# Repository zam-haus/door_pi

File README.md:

# door_pi

Controls electric door locks/openers via GPIO or a USB-serial microcontroller,
and exposes them over MQTT (see `door_manager/`). `uc/` is the firmware that
runs on the microcontroller for the USB HAL variant.

## Running the simulation

`run_simulation.py` runs the real `door_manager` (including a real MQTT
connection) against an in-process simulated microcontroller
(`DoorHalUsbSimulatedUc` in `door_manager/door_hal.py`), so you can exercise
the whole stack without any hardware attached.

1. Install both `door_manager` and `uc` as editable packages into the project
   venv (only needed once, or after changing dependencies):

   ```sh
   uv sync
   ```

2. Start a local MQTT broker with the compose file in `testing/`:

   ```sh
   (cd testing; podman compose up -d --build)   # or: docker compose up -d --build
   ```

   This builds `testing/mosquitto/Dockerfile` (based on `eclipse-mosquitto`,
   with the config and password file baked in — see below) and starts it on
   `127.0.0.1:8001`, with auth for user/pass `test`/`test` — matching
   `door_manager/config.json.example-usb`, which the simulation uses by
   default.

   > If you have the `mosquitto` package installed on the host, its AppArmor
   > profile attaches by executable path (`/usr/sbin/mosquitto`), which
   > confines *this* container's mosquitto too on exec and blocks it from
   > reading its own config — regardless of container boundaries or
   > `--security-opt apparmor=unconfined`. `testing/mosquitto/Dockerfile`
   > works around this by copying the binary to a different path before
   > running it, so the host profile's attachment never matches. That's also
   > why the config/password file are baked into the image via `COPY`
   > rather than bind-mounted: the same host profile only allows the
   > mosquitto binary to read `/etc/mosquitto/**`.

3. Run the simulation:

   ```sh
   uv run run_simulation.py
   ```

   Pass `-c FILE` to point it at a different `door_manager` config.

   By default this also drives random simulated events, so you don't have
   to trigger everything by hand: the mode-switch buttons (`in1`/`in2`,
   `cycle-forward-input`/`cycle-backward-input` in the config) get pressed
   at random, and a simulated door-position sensor reacts to open impulses
   on `out3` -- except sometimes (by default 20% of the time) it doesn't,
   to exercise a flaky-sensor path. Every simulated event is logged with a
   `SIM:` prefix. Tune or disable this with:

   ```
   --no-random-events               turn it off entirely
   --button-min=SECONDS              min delay between button presses [default: 1.5]
   --button-max=SECONDS              max delay between button presses [default: 4.0]
   --pulse-hold=SECONDS               how long a button press is held [default: 0.3]
   --malfunction-rate=RATE            chance (0-1) the door sensor misses an open [default: 0.2]
   --sensor-check-interval=SECONDS   how often the sensor polls for an open impulse [default: 0.05]
   ```

4. When done, stop the broker:

   ```sh
   cd testing
   podman compose down   # or: docker compose down
   ```

## Sending MQTT messages

The `eclipse-mosquitto` image bundles the `mosquitto_pub`/`mosquitto_sub`
CLI tools, so you don't need to install an MQTT client locally — just run
them inside the broker container via `podman compose exec` (from the
`testing/` directory, with the broker already up). Use `localhost`/`1883`
(the container's own view of the broker), not the host-mapped `8001`.

Watch everything the door publishes and any commands sent to it:

```sh
(cd testing; podman compose exec mosquitto mosquitto_sub -h localhost -p 1883 \
  -u test -P test -t 'door/#' -v)
```

Send an open command (door-id `1234`, matching
`door_manager/config.json.example-usb`) — `not_after` is a Unix timestamp
the request must arrive before:

```sh
(cd testing; podman compose exec mosquitto mosquitto_pub -h localhost -p 1883 \
  -u test -P test -t door/1234/open -m "{\"not_after\": $(($(date +%s) + 60))}")
```

With the simulation running, this should trigger `DoorManager.open_door()`
and impulse the configured output GPIOs on the simulated microcontroller.

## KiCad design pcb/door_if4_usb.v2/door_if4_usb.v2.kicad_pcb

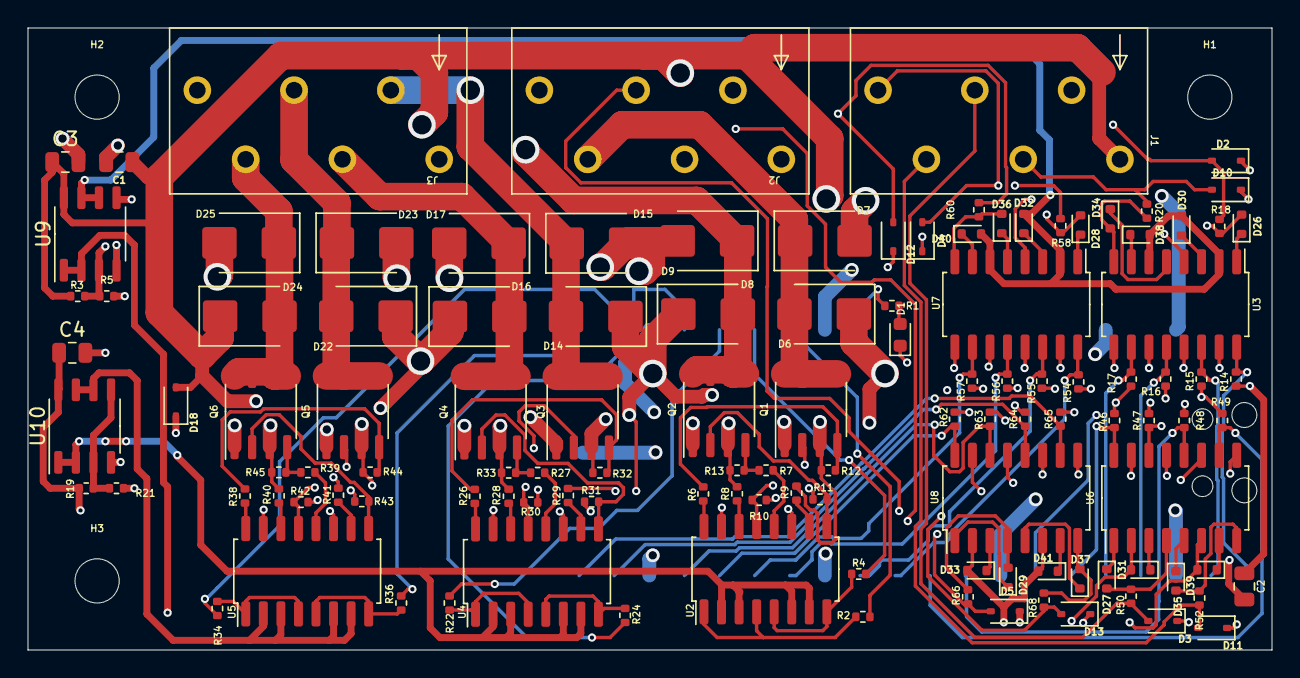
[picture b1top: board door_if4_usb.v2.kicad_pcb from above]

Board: 4 copper layers, 90.0 x 45.0 mm, 123 parts (1 on the bottom side), 102 nets.

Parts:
C1, C2, C3, C4: 100n/50V; C_0805_2012Metric
D1: LED; LED_0603_1608Metric
D2, D3, D4, D5, D10, D11, D12, D13, D18: LY323DC24; D_SOD-323
D6, D7, D8, D9, D14, D15, D16, D17, D22, D23, D24, D25: SS24B; D_SMB
D26, D27, D28, D29, D30, D31, D32, D33, D34, D35, D36, D37, D38, D39, D40, D41: D; D_SOD-523
H1, H2, H3: MountingHole; MountingHole_3.2mm_M3_DIN965
J1, J2, J3: WAGO 250-206; WAGO-250-206
Q1, Q2, Q3, Q4, Q5, Q6: IRF7343; SO-8_3.9x4.9mm_P1.27mm
R1: 470; R_0402_1005Metric
R2, R4, R22, R24, R34, R36: 120; R_0402_1005Metric
R3, R5, R6, R7, R8, R9, R10, R11, R12, R13, R19, R21, R26, R27, R28, R29, R30, R31, R32, R33, R38, R39, R40, R41, R42, R43, R44, R45: 10k; R_0402_1005Metric
R14, R15, R16, R17, R18, R20, R46, R47, R48, R49, R50, R52, R54, R55, R56, R57, R58, R60, R62, R63, R64, R65, R66, R68: 2k2; R_0402_1005Metric
U1: Pico; RPi_Pico_SMDonly
U2, U3, U4, U5, U6, U7, U8: LTV-247; SOP-16_4.4x10.4mm_P1.27mm
U9, U10: COS2171; SOP-8_3.9x4.9mm_P1.27mm

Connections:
+3V3: C2.1, C4.1, R14.1, R15.1, R16.1, R17.1, R19.1, R46.1, R47.1, R48.1, R49.1, R54.1, R55.1, R56.1, R57.1, R62.1, R63.1, R64.1, R65.1, U1.36 (3V3), U10.8 (V+)
+24V: C1.1, C3.1, D6.1 (K), D8.1 (K), D14.1 (K), D16.1 (K), D18.2 (A2), D22.1 (K), D24.1 (K), J1.1, J2.1, Q1.3 (S2), Q2.3 (S2), Q3.3 (S2), Q4.3 (S2), Q5.3 (S2), Q6.3 (S2), R3.1, R8.2, R9.2, R12.2, R13.2, R28.2, R29.2, R32.2, R33.2, R40.2, R41.2, R44.2, R45.2, U9.8 (V+)
GND: C2.2, C4.2, D1.1 (K), R21.2, U1.3 (GND), U1.8 (GND), U1.13 (GND), U1.18 (GND), U1.23 (GND), U1.28 (GND), U1.38 (GND), U1.42 (GND), U3.9, U3.11, U3.13, U3.15, U6.9, U6.11, U6.13, U6.15, U7.9, U7.11, U7.13, U7.15, U8.9, U8.11, U8.13, U8.15, U10.4 (V-)
GNDA: C1.2, C3.2, D2.1 (A1), D3.1 (A1), D4.1 (A1), D5.1 (A1), D7.2 (A), D9.2 (A), D10.1 (A1), D11.1 (A1), D12.1 (A1), D13.1 (A1), D15.2 (A), D17.2 (A), D18.1 (A1), D23.2 (A), D25.2 (A), J2.6, J3.6, Q1.1 (S1), Q2.1 (S1), Q3.1 (S1), Q4.1 (S1), Q5.1 (S1), Q6.1 (S1), R5.2, R10.1, R11.1, R30.1, R31.1, R42.1, R43.1, U2.11, U2.15, U4.11, U4.15, U5.11, U5.15, U9.4 (V-)
IN1: D2.2 (A2), J1.2, R18.2
IN2: D10.2 (A2), J1.3, R20.2
IN3: D3.2 (A2), J1.4, R50.2
IN4: D11.2 (A2), J1.5, R52.2
IN5: D4.2 (A2), J1.6, R58.2
IN6: D12.2 (A2), J2.2, R60.2
IN7: D5.2 (A2), J2.3, R66.2
IN8: D13.2 (A2), J2.4, R68.2
unnamed: D1.2 (A), R1.1
unnamed: D26.2 (A), R18.1, U3.4
unnamed: D26.1 (K), U3.1
unnamed: D27.2 (A), R50.1, U6.4
unnamed: D27.1 (K), U6.1
unnamed: D28.2 (A), R58.1, U7.4
unnamed: D28.1 (K), U7.1
unnamed: D29.2 (A), R66.1, U8.4
unnamed: D29.1 (K), U8.1
unnamed: D30.1 (K), U3.3
unnamed: D31.1 (K), U6.3
unnamed: D32.1 (K), U7.3
unnamed: D33.1 (K), U8.3
unnamed: D34.2 (A), R20.1, U3.8
unnamed: D34.1 (K), U3.5
unnamed: D35.2 (A), R52.1, U6.8
unnamed: D35.1 (K), U6.5
unnamed: D36.2 (A), R60.1, U7.8
unnamed: D36.1 (K), U7.5
unnamed: D37.2 (A), R68.1, U8.8
unnamed: D37.1 (K), U8.5
unnamed: D38.1 (K), U3.7
unnamed: D39.1 (K), U6.7
unnamed: D40.1 (K), U7.7
unnamed: D41.1 (K), U8.7
unnamed: Q1.2 (G1), R10.2, U2.13
unnamed: Q1.4 (G2), R6.2, R12.1
unnamed: Q2.2 (G1), R11.2, U2.9
unnamed: Q2.4 (G2), R7.2, R13.1
unnamed: Q3.2 (G1), R30.2, U4.13
unnamed: Q3.4 (G2), R26.2, R32.1
unnamed: Q4.2 (G1), R31.2, U4.9
unnamed: Q4.4 (G2), R27.2, R33.1
unnamed: Q5.2 (G1), R42.2, U5.13
unnamed: Q5.4 (G2), R38.2, R44.1
unnamed: Q6.2 (G1), R43.2, U5.9
unnamed: Q6.4 (G2), R39.2, R45.1
unnamed: R2.2, U2.1, U2.4
unnamed: R4.2, U2.5, U2.8
unnamed: R6.1, U2.16
unnamed: R7.1, U2.12
unnamed: R8.1, U2.14
unnamed: R9.1, U2.10
unnamed: R22.2, U4.1, U4.4
unnamed: R24.2, U4.5, U4.8
unnamed: R26.1, U4.16
unnamed: R27.1, U4.12
unnamed: R28.1, U4.14
unnamed: R29.1, U4.10
unnamed: R34.2, U5.1, U5.4
unnamed: R36.2, U5.5, U5.8
unnamed: R38.1, U5.16
unnamed: R39.1, U5.12
unnamed: R40.1, U5.14
unnamed: R41.1, U5.10
unnamed: R3.2, R5.1, U9.3 (+), U9.5 (+)
unnamed: R19.2, R21.1, U10.3 (+), U10.5 (+)
OUT1: D6.2 (A), D7.1 (K), J2.5, Q1.5 (D), Q1.6 (D), Q1.7 (D), Q1.8 (D)
OUT2: D8.2 (A), D9.1 (K), J3.1, Q2.5 (D), Q2.6 (D), Q2.7 (D), Q2.8 (D)
OUT3: D14.2 (A), D15.1 (K), J3.2, Q3.5 (D), Q3.6 (D), Q3.7 (D), Q3.8 (D)
OUT4: D16.2 (A), D17.1 (K), J3.3, Q4.5 (D), Q4.6 (D), Q4.7 (D), Q4.8 (D)
OUT5: D22.2 (A), D23.1 (K), J3.4, Q5.5 (D), Q5.6 (D), Q5.7 (D), Q5.8 (D)
OUT6: D24.2 (A), D25.1 (K), J3.5, Q6.5 (D), Q6.6 (D), Q6.7 (D), Q6.8 (D)
O_LED: R1.2, U1.29 (GPIO22)
S_IN1A: R14.2, U1.1 (GPIO0), U3.16
S_IN1B: R15.2, U1.2 (GPIO1), U3.14
S_IN2A: R16.2, U1.4 (GPIO2), U3.12
S_IN2B: R17.2, U1.5 (GPIO3), U3.10
S_IN3A: R46.2, U1.6 (GPIO4), U6.16
S_IN3B: R47.2, U1.7 (GPIO5), U6.14
S_IN4A: R48.2, U1.9 (GPIO6), U6.12
S_IN4B: R49.2, U1.10 (GPIO7), U6.10
S_IN5A: R54.2, U1.11 (GPIO8), U7.16
S_IN5B: R55.2, U1.12 (GPIO9), U7.14
S_IN6A: R56.2, U1.14 (GPIO10), U7.12
S_IN6B: R57.2, U1.15 (GPIO11), U7.10
S_IN7A: R62.2, U1.16 (GPIO12), U8.16
S_IN7B: R63.2, U1.17 (GPIO13), U8.14
S_IN8A: R64.2, U1.19 (GPIO14), U8.12
S_IN8B: R65.2, U1.20 (GPIO15), U8.10
S_OUT1: R2.1, U1.27 (GPIO21)
S_OUT2: R4.1, U1.26 (GPIO20)
S_OUT3: R22.1, U1.25 (GPIO19)
S_OUT4: R24.1, U1.24 (GPIO18)
S_OUT5: R34.1, U1.22 (GPIO17)
S_OUT6: R36.1, U1.21 (GPIO16)
VmidA: D31.2 (A), D33.2 (A), D39.2 (A), D41.2 (A), U6.2, U6.6, U8.2, U8.6, U9.1, U9.2 (-)
VmidB: D30.2 (A), D32.2 (A), D38.2 (A), D40.2 (A), U3.2, U3.6, U7.2, U7.6, U9.6 (-), U9.7
Vmid_3v3_A: U2.2, U2.3, U2.6, U2.7, U4.2, U4.3, U4.6, U4.7, U10.1, U10.2 (-)
Vmid_3v3_B: U5.2, U5.3, U5.6, U5.7, U10.6 (-), U10.7

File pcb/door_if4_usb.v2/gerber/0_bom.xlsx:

Comment | Designator | Footprint
LY323DC24 | D2,D10,D12,D18,D3,D5,D13,D4,D11 | D_SOD-323
D | D28,D31,D34,D27,D35,D33,D30,D39,D37,D29,D38,D32,D41,D40,D26,D36 | D_SOD-523
SS24B | D24,D7,D22,D9,D16,D25,D8,D23,D17,D14,D15,D6 | D_SMB
10k | R8,R38,R21,R39,R5,R10,R29,R9,R45,R7,R31,R12,R11,R13,R30,R26,R27,R42,R3,R19,R33,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 | R_0402_1005Metric
2k2 | R60,R54,R17,R55,R20,R49,R66,R52,R64,R56,R47,R18,R16,R46,R57,R63,R68,R15,R50,R48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 | R_0402_1005Metric
120 | R22,R4,R2,R24,R36,R34 | R_0402_1005Metric
LTV-247 | U3,U7,U8,U4,U2,U6,U5 | SOP-16_4.4x10.4mm_P1.27mm
IRF7343 | Q4,Q6,Q1,Q5,Q2,Q3 | SO-8_3.9x4.9mm_P1.27mm
100n/50V | C3,C2,C4,C1 | C_0805_2012Metric
LED | D1 | LED_0603_1608Metric
COS2171 | U10,U9 | SOP-8_3.9x4.9mm_P1.27mm
470 | R1 | R_0402_1005Metric

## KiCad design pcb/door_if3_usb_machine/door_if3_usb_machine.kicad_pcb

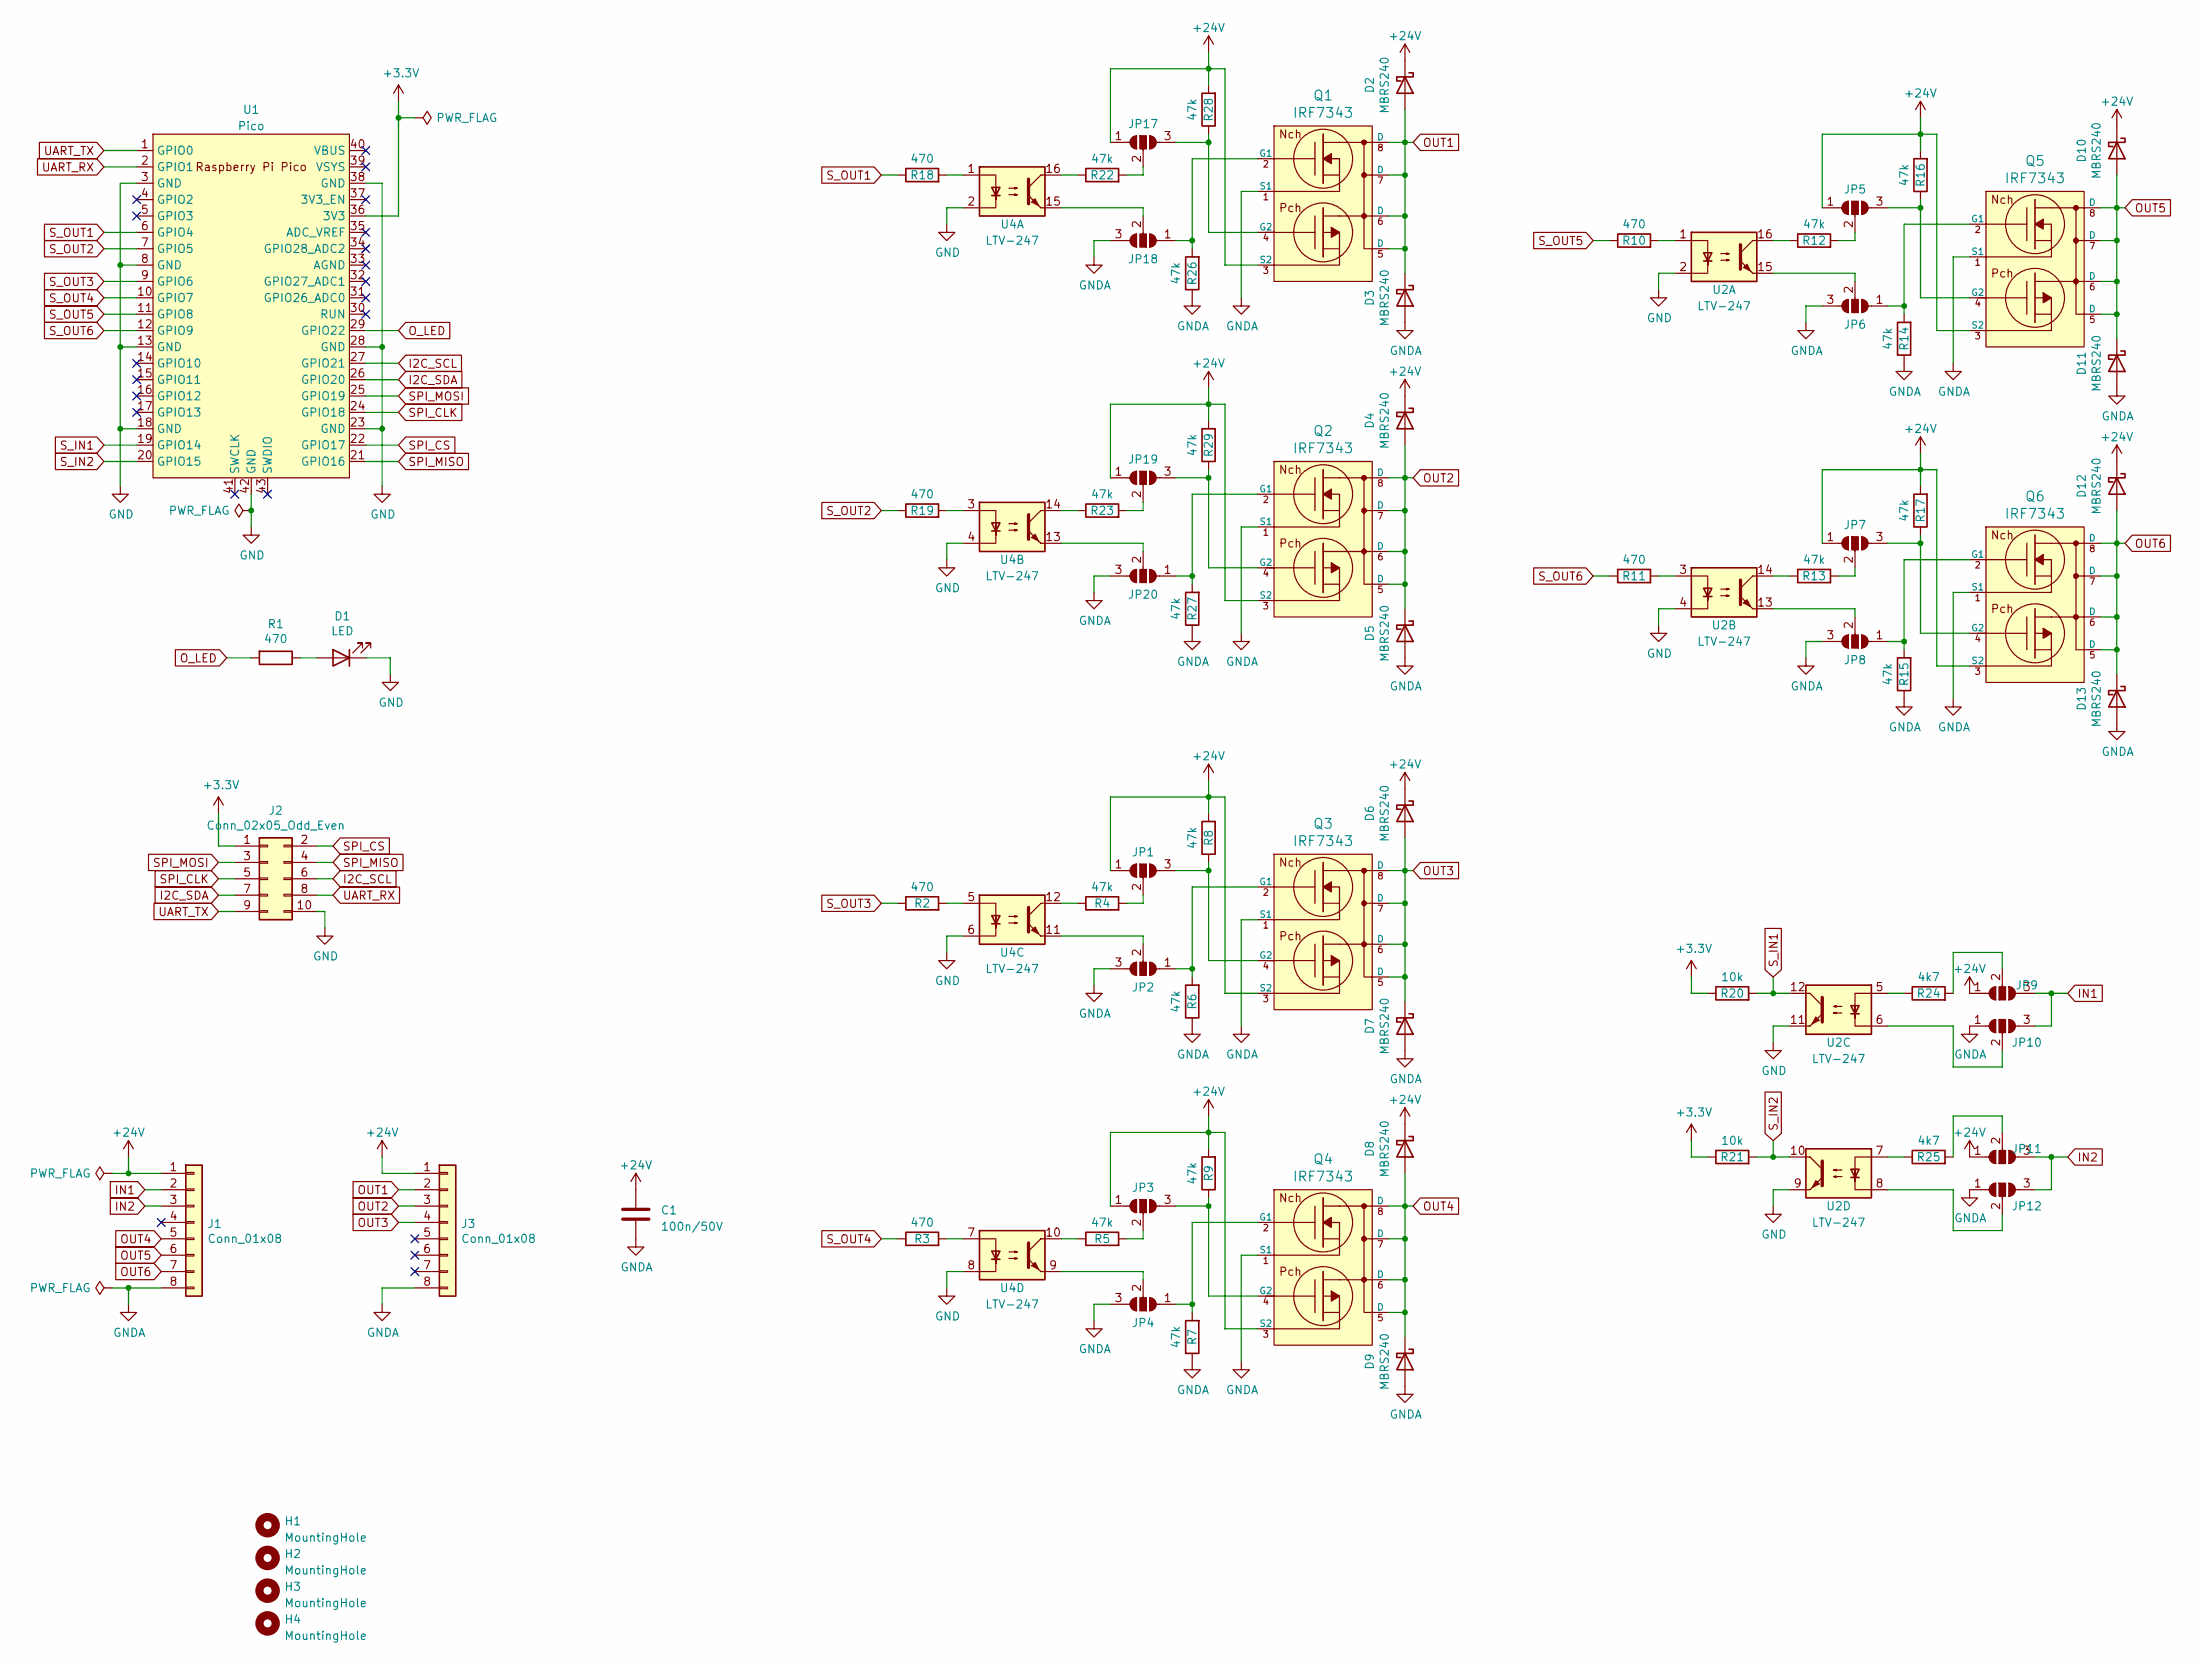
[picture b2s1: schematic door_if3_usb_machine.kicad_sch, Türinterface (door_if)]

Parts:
C1: 100n/50V; C_0603_1608Metric_Pad1.08x0.95mm_HandSolder
D1: LED; LED_0603_1608Metric_Pad1.05x0.95mm_HandSolder
D2, D3, D4, D5, D6, D7, D8, D9, D10, D11, D12, D13: MBRS240; D_SMB_Handsoldering
H1, H2, H3, H4: MountingHole; MountingHole_3.2mm_M3_DIN965
J1, J3: Conn_01x08; LSA-IDC381-8
J2: Conn_02x05_Odd_Even; con-harting-ml-ML10
JP1, JP2, JP3, JP4, JP5, JP6, JP7, JP8, JP9, JP10, JP11, JP12, JP17, JP18, JP19, JP20: SolderJumper_3_Open; SolderJumper-3_P1.3mm_Open_Pad1.0x1.5mm
Q1, Q2, Q3, Q4, Q5, Q6: IRF7343; SO-8_3.9x4.9mm_P1.27mm
R1, R2, R3, R10, R11, R18, R19: 470; R_0603_1608Metric_Pad0.98x0.95mm_HandSolder
R4, R5, R6, R7, R8, R9, R12, R13, R14, R15, R16, R17, R22, R23, R26, R27, R28, R29: 47k; R_0603_1608Metric_Pad0.98x0.95mm_HandSolder
R20, R21: 10k; R_0603_1608Metric_Pad0.98x0.95mm_HandSolder
R24, R25: 4k7; R_0603_1608Metric_Pad0.98x0.95mm_HandSolder
U1: Pico; RPi_Pico_SMDonly
U2, U4: LTV-247; SOP-16_4.4x10.4mm_P1.27mm

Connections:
+3V3: J2.1, R20.1, R21.1, U1.36 (3V3)
+24V: C1.1, D2.1 (K), D4.1 (K), D6.1 (K), D8.1 (K), D10.1 (K), D12.1 (K), J1.1, J3.1, JP1.1 (A), JP3.1 (A), JP5.1 (A), JP7.1 (A), JP9.1 (A), JP11.1 (A), JP17.1 (A), JP19.1 (A), Q1.3 (S2), Q2.3 (S2), Q3.3 (S2), Q4.3 (S2), Q5.3 (S2), Q6.3 (S2), R8.2, R9.2, R16.2, R17.2, R28.2, R29.2
GND: D1.1 (K), J2.10, U1.3 (GND), U1.8 (GND), U1.13 (GND), U1.18 (GND), U1.23 (GND), U1.28 (GND), U1.38 (GND), U1.42 (GND), U2.2, U2.4, U2.9, U2.11, U4.2, U4.4, U4.6, U4.8
GNDA: C1.2, D3.2 (A), D5.2 (A), D7.2 (A), D9.2 (A), D11.2 (A), D13.2 (A), J1.8, J3.8, JP2.3 (B), JP4.3 (B), JP6.3 (B), JP8.3 (B), JP10.1 (A), JP12.1 (A), JP18.3 (B), JP20.3 (B), Q1.1 (S1), Q2.1 (S1), Q3.1 (S1), Q4.1 (S1), Q5.1 (S1), Q6.1 (S1), R6.1, R7.1, R14.1, R15.1, R26.1, R27.1
I2C_SCL: J2.6, U1.27 (GPIO21)
I2C_SDA: J2.7, U1.26 (GPIO20)
IN1: J1.2, JP9.3 (B), JP10.3 (B)
IN2: J1.3, JP11.3 (B), JP12.3 (B)
unnamed: D1.2 (A), R1.1
unnamed: JP1.3 (B), Q3.4 (G2), R8.1
unnamed: JP1.2 (C), R4.2
unnamed: JP2.1 (A), Q3.2 (G1), R6.2
unnamed: JP2.2 (C), U4.11
unnamed: JP3.3 (B), Q4.4 (G2), R9.1
unnamed: JP3.2 (C), R5.2
unnamed: JP4.1 (A), Q4.2 (G1), R7.2
unnamed: JP4.2 (C), U4.9
unnamed: JP5.3 (B), Q5.4 (G2), R16.1
unnamed: JP5.2 (C), R12.2
unnamed: JP6.1 (A), Q5.2 (G1), R14.2
unnamed: JP6.2 (C), U2.15
unnamed: JP7.3 (B), Q6.4 (G2), R17.1
unnamed: JP7.2 (C), R13.2
unnamed: JP8.1 (A), Q6.2 (G1), R15.2
unnamed: JP8.2 (C), U2.13
unnamed: JP9.2 (C), R24.2
unnamed: JP10.2 (C), U2.6
unnamed: JP11.2 (C), R25.2
unnamed: JP12.2 (C), U2.8
unnamed: JP17.3 (B), Q1.4 (G2), R28.1
unnamed: JP17.2 (C), R22.2
unnamed: JP18.1 (A), Q1.2 (G1), R26.2
unnamed: JP18.2 (C), U4.15
unnamed: JP19.3 (B), Q2.4 (G2), R29.1
unnamed: JP19.2 (C), R23.2
unnamed: JP20.1 (A), Q2.2 (G1), R27.2
unnamed: JP20.2 (C), U4.13
unnamed: R2.2, U4.5
unnamed: R3.2, U4.7
unnamed: R4.1, U4.12
unnamed: R5.1, U4.10
unnamed: R10.2, U2.1
unnamed: R11.2, U2.3
unnamed: R12.1, U2.16
unnamed: R13.1, U2.14
unnamed: R18.2, U4.1
unnamed: R19.2, U4.3
unnamed: R22.1, U4.16
unnamed: R23.1, U4.14
unnamed: R24.1, U2.5
unnamed: R25.1, U2.7
OUT1: D2.2 (A), D3.1 (K), J3.2, Q1.5 (D), Q1.6 (D), Q1.7 (D), Q1.8 (D)
OUT2: D4.2 (A), D5.1 (K), J3.3, Q2.5 (D), Q2.6 (D), Q2.7 (D), Q2.8 (D)
OUT3: D6.2 (A), D7.1 (K), J3.4, Q3.5 (D), Q3.6 (D), Q3.7 (D), Q3.8 (D)
OUT4: D8.2 (A), D9.1 (K), J1.5, Q4.5 (D), Q4.6 (D), Q4.7 (D), Q4.8 (D)
OUT5: D10.2 (A), D11.1 (K), J1.6, Q5.5 (D), Q5.6 (D), Q5.7 (D), Q5.8 (D)
OUT6: D12.2 (A), D13.1 (K), J1.7, Q6.5 (D), Q6.6 (D), Q6.7 (D), Q6.8 (D)
O_LED: R1.2, U1.29 (GPIO22)
SPI_CLK: J2.5, U1.24 (GPIO18)
SPI_CS: J2.2, U1.22 (GPIO17)
SPI_MISO: J2.4, U1.21 (GPIO16)
SPI_MOSI: J2.3, U1.25 (GPIO19)
S_IN1: R20.2, U1.19 (GPIO14), U2.12
S_IN2: R21.2, U1.20 (GPIO15), U2.10
S_OUT1: R18.1, U1.6 (GPIO4)
S_OUT2: R19.1, U1.7 (GPIO5)
S_OUT3: R2.1, U1.9 (GPIO6)
S_OUT4: R3.1, U1.10 (GPIO7)
S_OUT5: R10.1, U1.11 (GPIO8)
S_OUT6: R11.1, U1.12 (GPIO9)
UART_RX: J2.8, U1.2 (GPIO1)
UART_TX: J2.9, U1.1 (GPIO0)

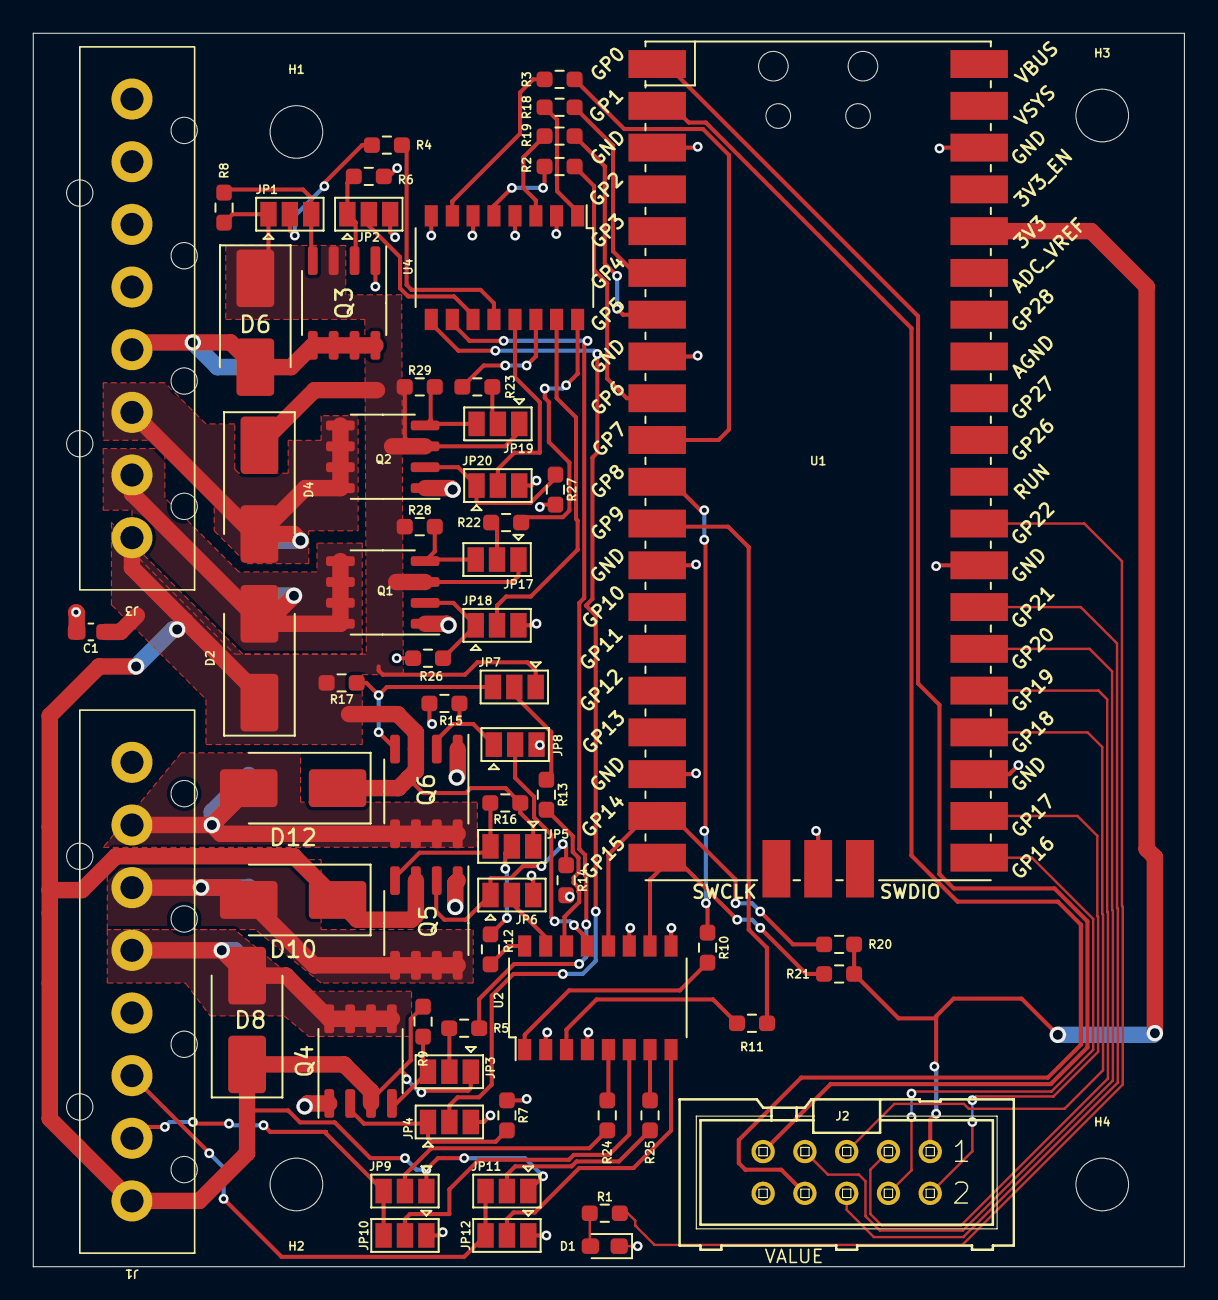
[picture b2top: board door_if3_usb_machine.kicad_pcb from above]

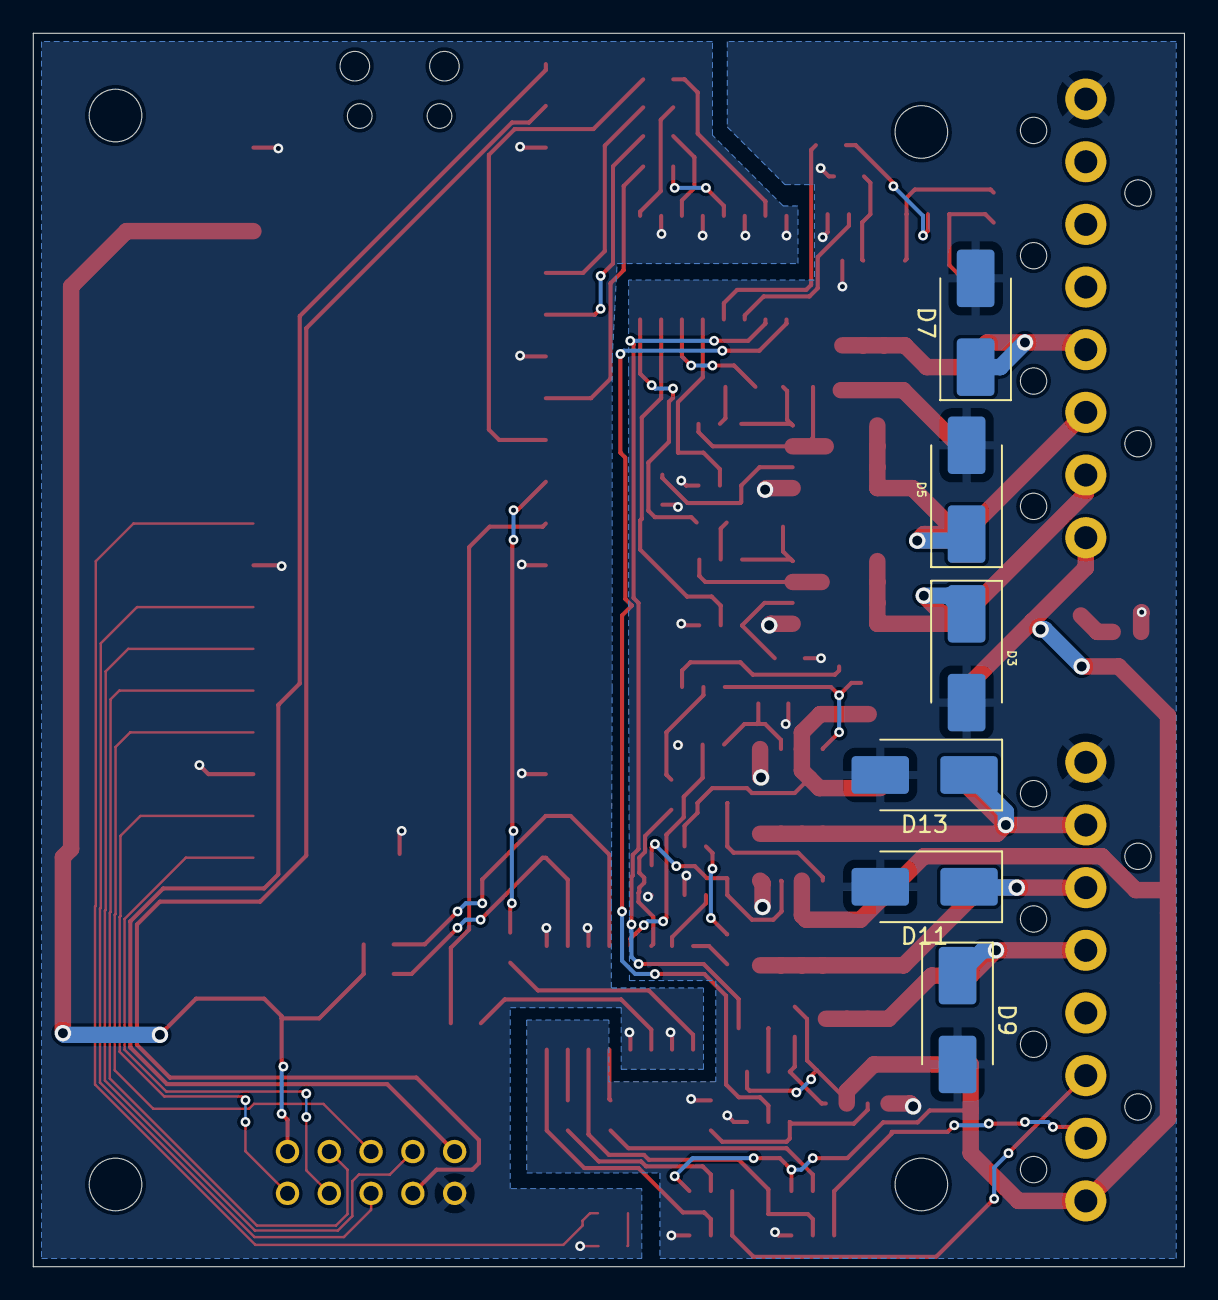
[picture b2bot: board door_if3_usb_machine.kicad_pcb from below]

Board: 2 copper layers, 70.0 x 75.0 mm, 75 parts (6 on the bottom side), 72 nets.

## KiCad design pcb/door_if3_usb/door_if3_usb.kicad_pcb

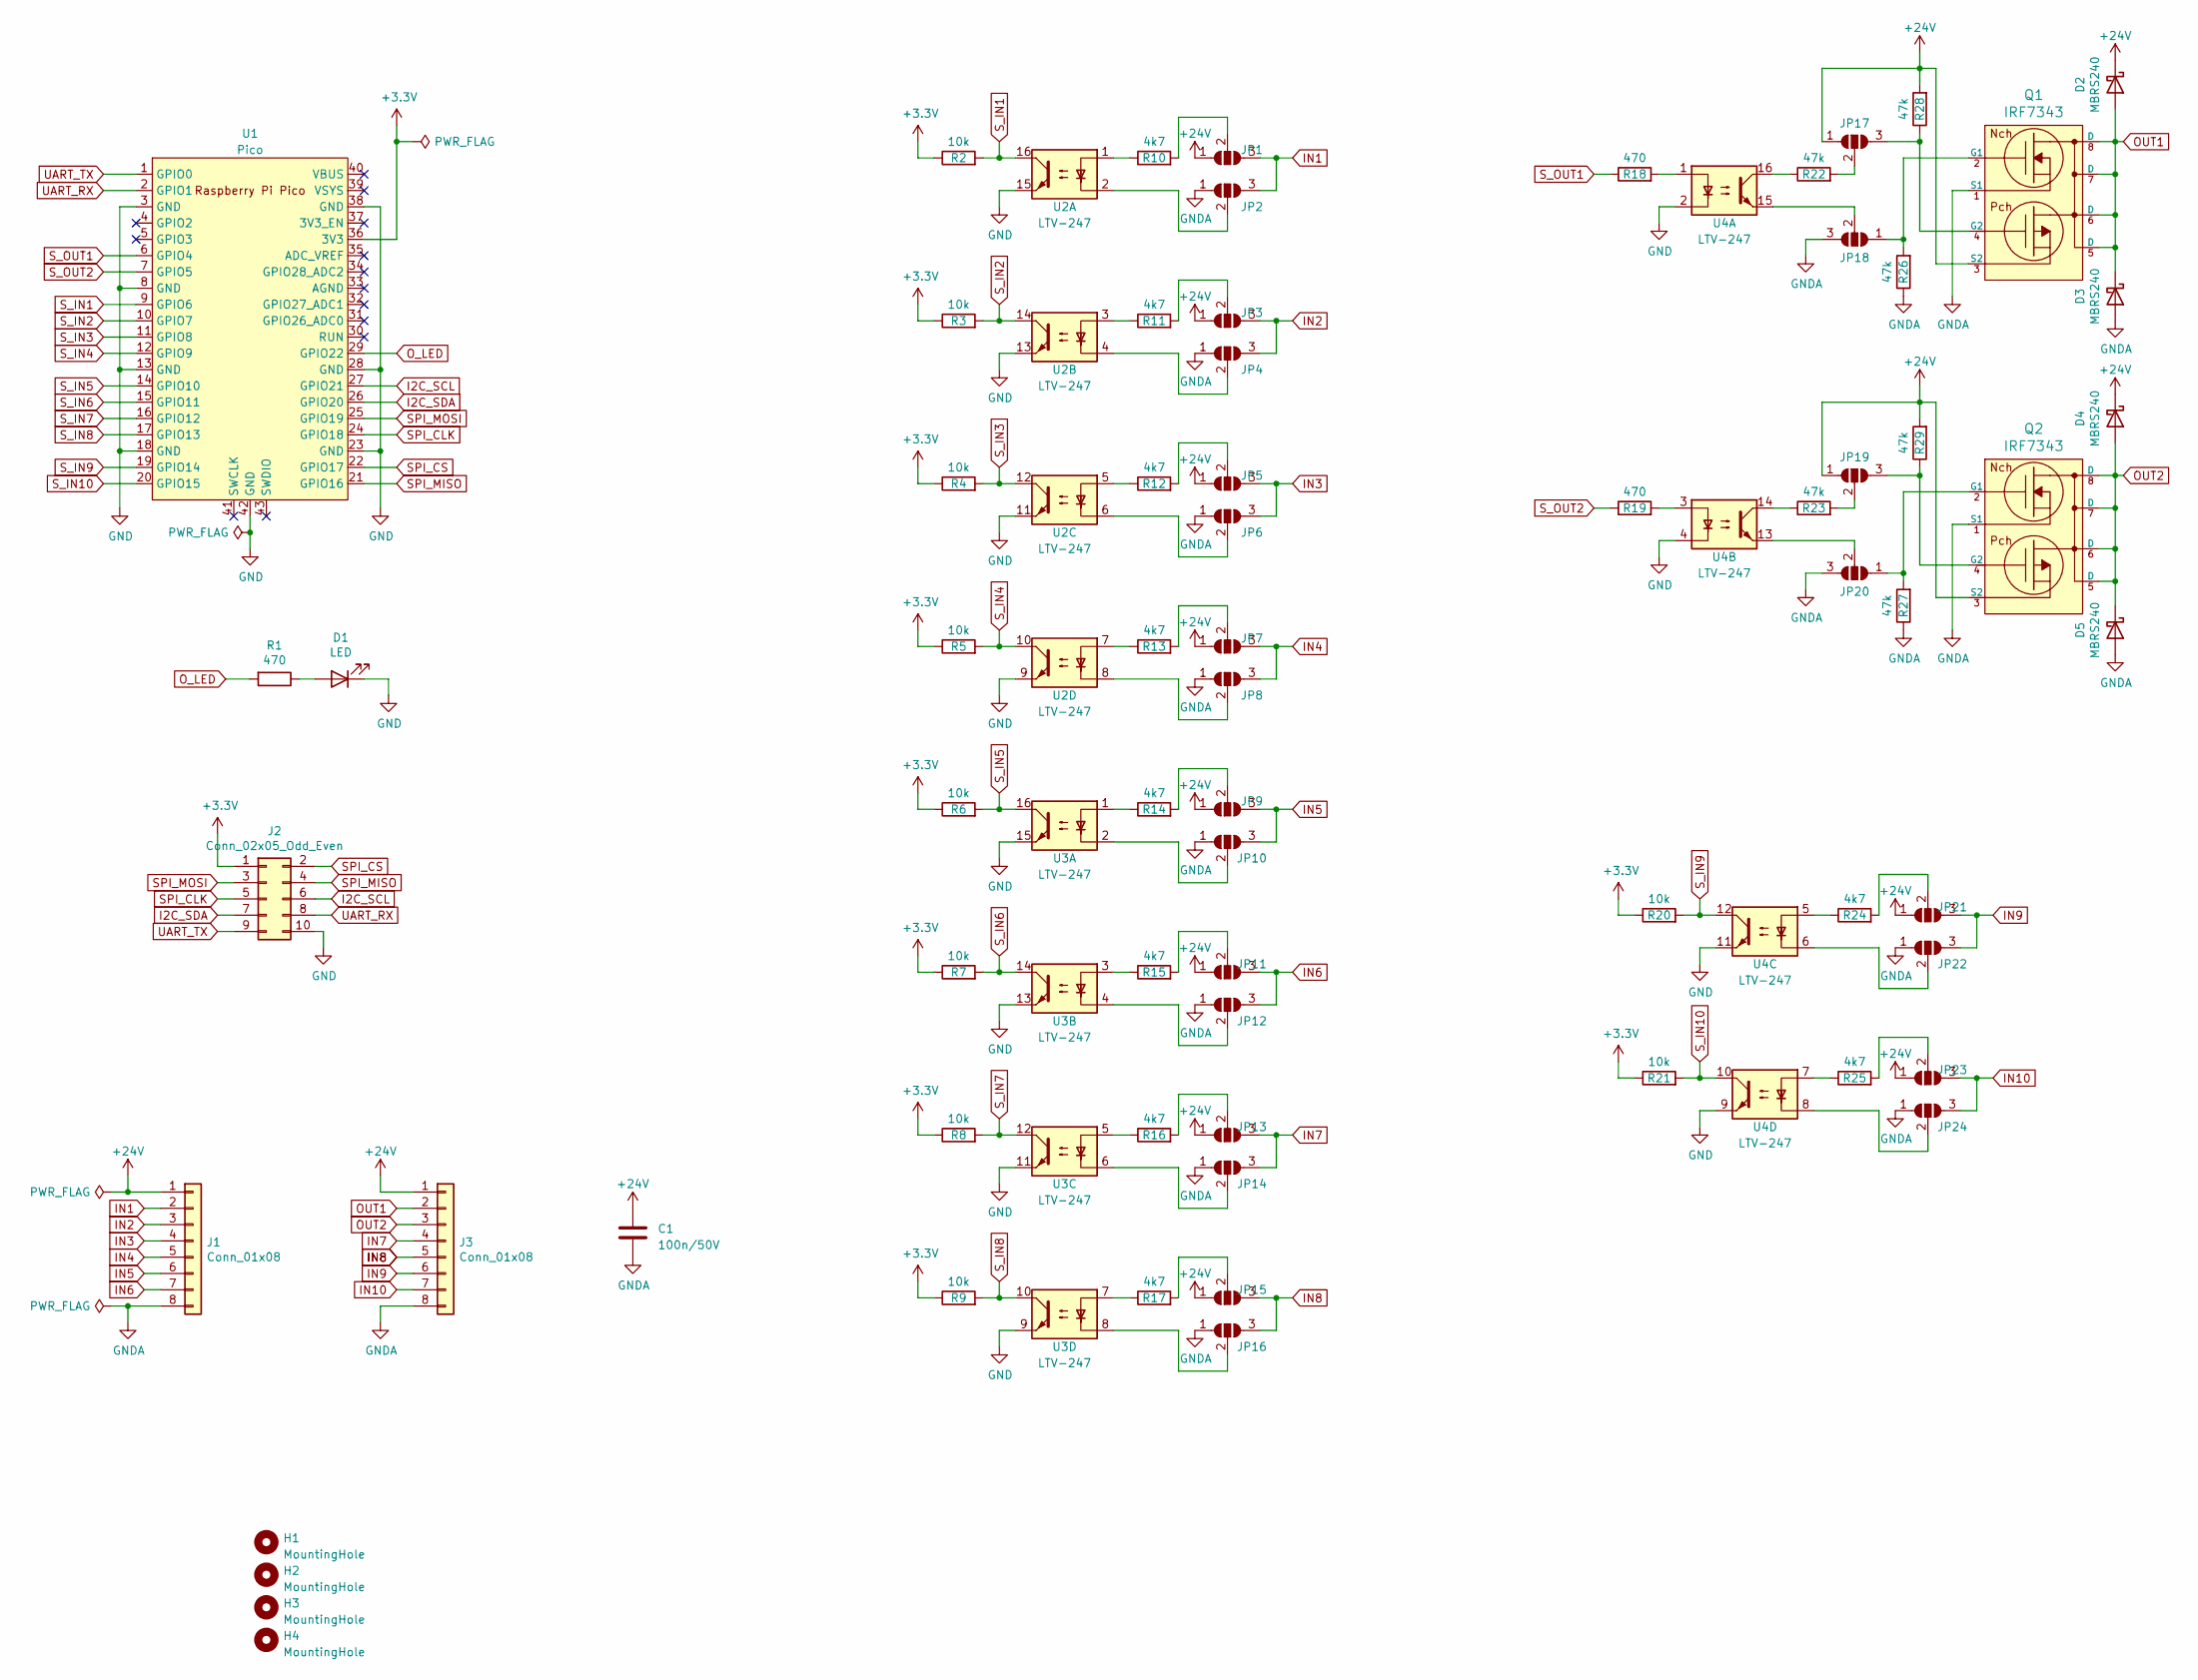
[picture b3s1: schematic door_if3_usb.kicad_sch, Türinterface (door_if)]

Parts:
C1: 100n/50V; C_0603_1608Metric_Pad1.08x0.95mm_HandSolder
D1: LED; LED_0603_1608Metric_Pad1.05x0.95mm_HandSolder
D2, D3, D4, D5: MBRS240; D_SMB_Handsoldering
H1, H2, H3, H4: MountingHole; MountingHole_3.2mm_M3_DIN965
J1, J3: Conn_01x08; LSA-IDC381-8
J2: Conn_02x05_Odd_Even; con-harting-ml-ML10
JP1, JP2, JP3, JP4, JP5, JP6, JP7, JP8, JP9, JP10, JP11, JP12, JP13, JP14, JP15, JP16, JP17, JP18, JP19, JP20, JP21, JP22, JP23, JP24: SolderJumper_3_Open; SolderJumper-3_P1.3mm_Open_Pad1.0x1.5mm
Q1, Q2: IRF7343; SO-8_3.9x4.9mm_P1.27mm
R1, R18, R19: 470; R_0603_1608Metric_Pad0.98x0.95mm_HandSolder
R2, R3, R4, R5, R6, R7, R8, R9, R20, R21: 10k; R_0603_1608Metric_Pad0.98x0.95mm_HandSolder
R10, R11, R12, R13, R14, R15, R16, R17, R24, R25: 4k7; R_0603_1608Metric_Pad0.98x0.95mm_HandSolder
R22, R23, R26, R27, R28, R29: 47k; R_0603_1608Metric_Pad0.98x0.95mm_HandSolder
U1: Pico; RPi_Pico_SMDonly
U2, U3, U4: LTV-247; SOP-16_4.4x10.4mm_P1.27mm

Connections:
+3V3: J2.1, R2.1, R3.1, R4.1, R5.1, R6.1, R7.1, R8.1, R9.1, R20.1, R21.1, U1.36 (3V3)
+24V: C1.1, D2.1 (K), D4.1 (K), J1.1, J3.1, JP1.1 (A), JP3.1 (A), JP5.1 (A), JP7.1 (A), JP9.1 (A), JP11.1 (A), JP13.1 (A), JP15.1 (A), JP17.1 (A), JP19.1 (A), JP21.1 (A), JP23.1 (A), Q1.3 (S2), Q2.3 (S2), R28.2, R29.2
GND: D1.1 (K), J2.10, U1.3 (GND), U1.8 (GND), U1.13 (GND), U1.18 (GND), U1.23 (GND), U1.28 (GND), U1.38 (GND), U1.42 (GND), U2.9, U2.11, U2.13, U2.15, U3.9, U3.11, U3.13, U3.15, U4.2, U4.4, U4.9, U4.11
GNDA: C1.2, D3.2 (A), D5.2 (A), J1.8, J3.8, JP2.1 (A), JP4.1 (A), JP6.1 (A), JP8.1 (A), JP10.1 (A), JP12.1 (A), JP14.1 (A), JP16.1 (A), JP18.3 (B), JP20.3 (B), JP22.1 (A), JP24.1 (A), Q1.1 (S1), Q2.1 (S1), R26.1, R27.1
I2C_SCL: J2.6, U1.27 (GPIO21)
I2C_SDA: J2.7, U1.26 (GPIO20)
IN1: J1.2, JP1.3 (B), JP2.3 (B)
IN2: J1.3, JP3.3 (B), JP4.3 (B)
IN3: J1.4, JP5.3 (B), JP6.3 (B)
IN4: J1.5, JP7.3 (B), JP8.3 (B)
IN5: J1.6, JP9.3 (B), JP10.3 (B)
IN6: J1.7, JP11.3 (B), JP12.3 (B)
IN7: J3.4, JP13.3 (B), JP14.3 (B)
IN8: J3.5, JP15.3 (B), JP16.3 (B)
IN9: J3.6, JP21.3 (B), JP22.3 (B)
IN10: J3.7, JP23.3 (B), JP24.3 (B)
unnamed: D1.2 (A), R1.1
unnamed: JP1.2 (C), R10.2
unnamed: JP2.2 (C), U2.2
unnamed: JP3.2 (C), R11.2
unnamed: JP4.2 (C), U2.4
unnamed: JP5.2 (C), R12.2
unnamed: JP6.2 (C), U2.6
unnamed: JP7.2 (C), R13.2
unnamed: JP8.2 (C), U2.8
unnamed: JP9.2 (C), R14.2
unnamed: JP10.2 (C), U3.2
unnamed: JP11.2 (C), R15.2
unnamed: JP12.2 (C), U3.4
unnamed: JP13.2 (C), R16.2
unnamed: JP14.2 (C), U3.6
unnamed: JP15.2 (C), R17.2
unnamed: JP16.2 (C), U3.8
unnamed: JP17.3 (B), Q1.4 (G2), R28.1
unnamed: JP17.2 (C), R22.2
unnamed: JP18.1 (A), Q1.2 (G1), R26.2
unnamed: JP18.2 (C), U4.15
unnamed: JP19.3 (B), Q2.4 (G2), R29.1
unnamed: JP19.2 (C), R23.2
unnamed: JP20.1 (A), Q2.2 (G1), R27.2
unnamed: JP20.2 (C), U4.13
unnamed: JP21.2 (C), R24.2
unnamed: JP22.2 (C), U4.6
unnamed: JP23.2 (C), R25.2
unnamed: JP24.2 (C), U4.8
unnamed: R10.1, U2.1
unnamed: R11.1, U2.3
unnamed: R12.1, U2.5
unnamed: R13.1, U2.7
unnamed: R14.1, U3.1
unnamed: R15.1, U3.3
unnamed: R16.1, U3.5
unnamed: R17.1, U3.7
unnamed: R18.2, U4.1
unnamed: R19.2, U4.3
unnamed: R22.1, U4.16
unnamed: R23.1, U4.14
unnamed: R24.1, U4.5
unnamed: R25.1, U4.7
OUT1: D2.2 (A), D3.1 (K), J3.2, Q1.5 (D), Q1.6 (D), Q1.7 (D), Q1.8 (D)
OUT2: D4.2 (A), D5.1 (K), J3.3, Q2.5 (D), Q2.6 (D), Q2.7 (D), Q2.8 (D)
O_LED: R1.2, U1.29 (GPIO22)
SPI_CLK: J2.5, U1.24 (GPIO18)
SPI_CS: J2.2, U1.22 (GPIO17)
SPI_MISO: J2.4, U1.21 (GPIO16)
SPI_MOSI: J2.3, U1.25 (GPIO19)
S_IN1: R2.2, U1.9 (GPIO6), U2.16
S_IN2: R3.2, U1.10 (GPIO7), U2.14
S_IN3: R4.2, U1.11 (GPIO8), U2.12
S_IN4: R5.2, U1.12 (GPIO9), U2.10
S_IN5: R6.2, U1.14 (GPIO10), U3.16
S_IN6: R7.2, U1.15 (GPIO11), U3.14
S_IN7: R8.2, U1.16 (GPIO12), U3.12
S_IN8: R9.2, U1.17 (GPIO13), U3.10
S_IN9: R20.2, U1.19 (GPIO14), U4.12
S_IN10: R21.2, U1.20 (GPIO15), U4.10
S_OUT1: R18.1, U1.6 (GPIO4)
S_OUT2: R19.1, U1.7 (GPIO5)
UART_RX: J2.8, U1.2 (GPIO1)
UART_TX: J2.9, U1.1 (GPIO0)
